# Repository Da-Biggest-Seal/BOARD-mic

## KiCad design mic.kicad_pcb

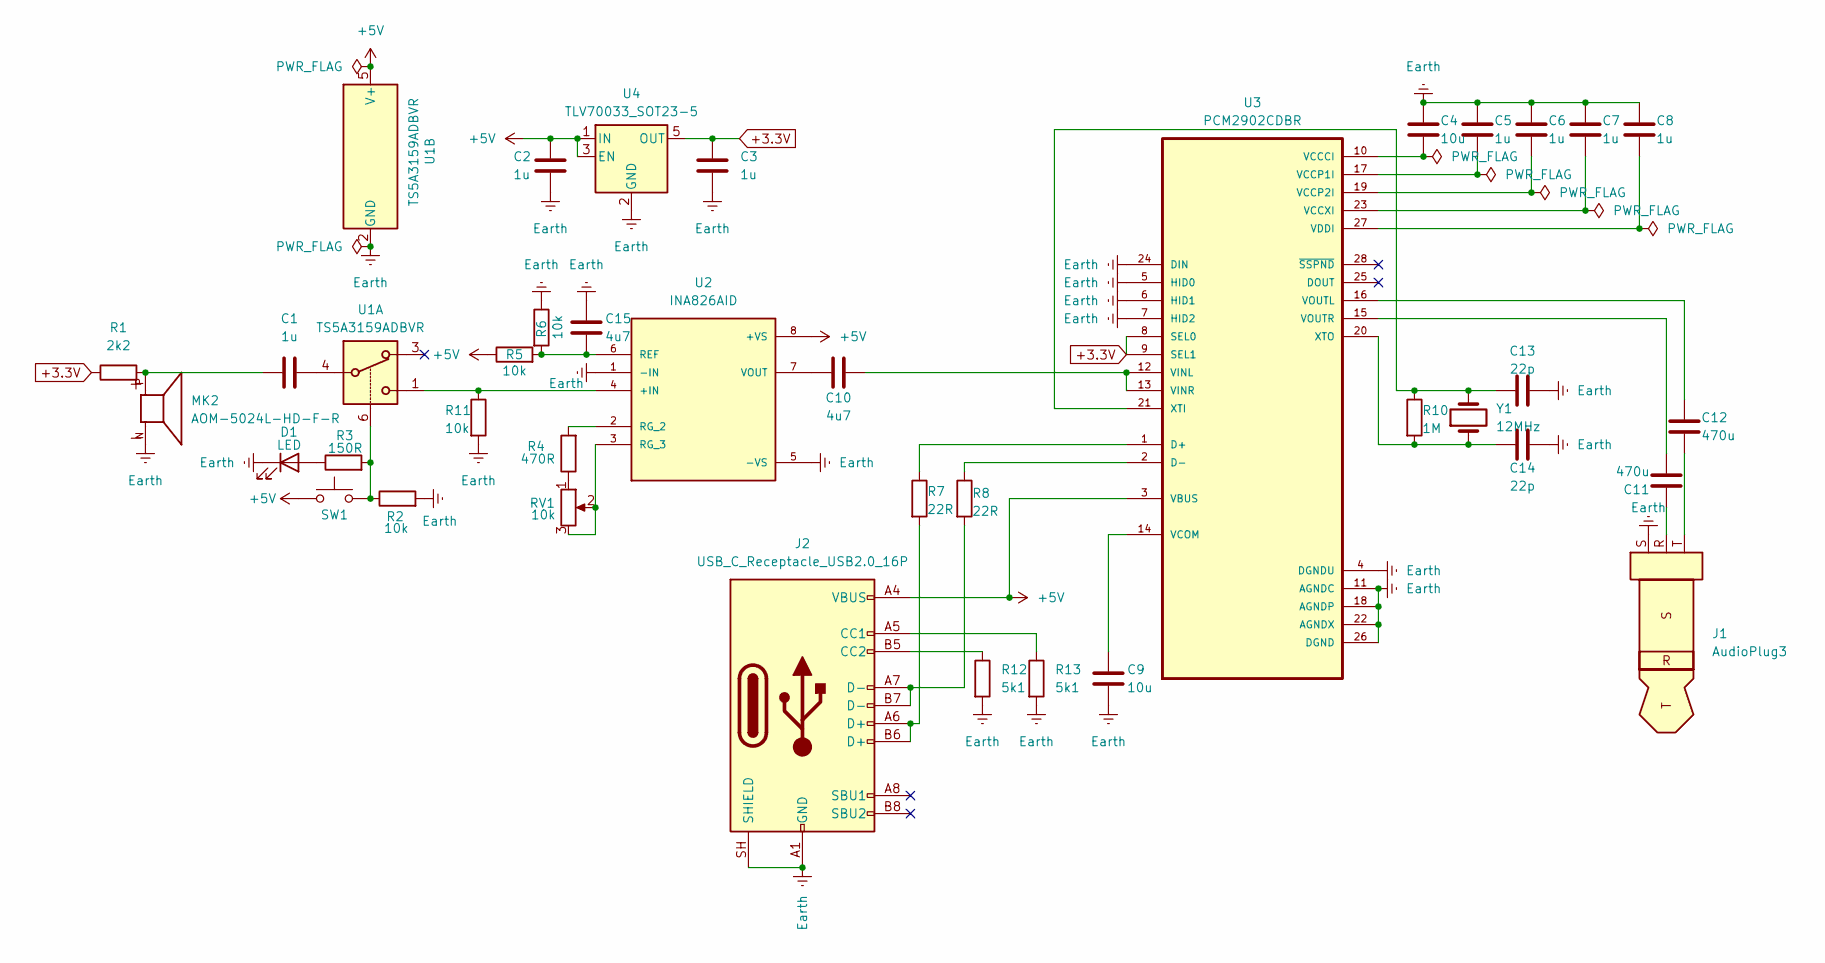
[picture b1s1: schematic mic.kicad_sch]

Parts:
C1, C2, C3, C5, C6, C7, C8: 1u; C_Disc_D3.4mm_W2.1mm_P2.50mm
C4, C9: 10u; C_Disc_D3.4mm_W2.1mm_P2.50mm
C10, C15: 4u7; C_Disc_D3.4mm_W2.1mm_P2.50mm
C11, C12: 470u; CP_Radial_D8.0mm_P3.50mm
C13, C14: 22p; C_Disc_D3.4mm_W2.1mm_P2.50mm
D1: LED; LED_D1.8mm_W1.8mm_H2.4mm_Horizontal_O1.27mm_Z1.6mm
J1: AudioPlug3; Jack_3.5mm_QingPu_WQP-PJ398SM_Vertical_CircularHoles; LCSC C22355828
J2: USB_C_Receptacle_USB2.0_16P; USB_C_Receptacle_G-Switch_GT-USB-7051x
MK2: AOM-5024L-HD-F-R; MIC_AOM-5024L-HD-F-R; PARTREV A
R1: 2k2; R_Axial_DIN0204_L3.6mm_D1.6mm_P2.54mm_Vertical
R2, R5, R6, R11: 10k; R_Axial_DIN0204_L3.6mm_D1.6mm_P2.54mm_Vertical
R3: 150R; R_Axial_DIN0204_L3.6mm_D1.6mm_P2.54mm_Vertical
R4: 470R; R_Axial_DIN0204_L3.6mm_D1.6mm_P2.54mm_Vertical
R7, R8: 22R; R_Axial_DIN0204_L3.6mm_D1.6mm_P2.54mm_Vertical
R10: 1M; R_Axial_DIN0204_L3.6mm_D1.6mm_P2.54mm_Vertical
R12, R13: 5k1; R_Axial_DIN0204_L3.6mm_D1.6mm_P2.54mm_Vertical
RV1: 10k; Potentiometer_Alps_RK097_Single_Horizontal
SW1: SW_Push; SW_Tactile_SPST_Angled_PTS645Vx58-2LFS
U1: TS5A3159ADBVR; SOT-23-6
U2: INA826AID; SOIC127P599X175-8N; PARTREV G; DigiKey_Part_Number 296-33294-5-ND
U3: PCM2902CDBR; SOP65P780X200-28N; DigiKey_Part_Number 2156-PCM2902CDBR-ND
U4: TLV70033_SOT23-5; SOT-23-5
Y1: 12MHz; Crystal_C26-LF_D2.1mm_L6.5mm_Vertical

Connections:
+3.3V: C3.1, R1.1, U3.8 (SEL0), U3.9 (SEL1), U4.5 (OUT)
+5V: C2.2, J2.A4 (VBUS), J2.A9 (VBUS), J2.B4 (VBUS), J2.B9 (VBUS), R5.1, SW1.1, U1.5 (V+), U2.8 (+VS), U3.3 (VBUS), U4.1 (IN), U4.3 (EN)
Earth: C2.1, C3.2, C4.1, C5.1, C6.1, C7.1, C8.1, C9.2, C13.2, C14.2, C15.1, D1.1 (K), J1.S, J2.A1 (GND), J2.A12 (GND), J2.B1 (GND), J2.B12 (GND), J2.SH (SHIELD), MK2.N, R2.2, R6.1, R11.2, R12.2, R13.2, U1.2 (GND), U2.1 (-IN), U2.5 (-VS), U3.4 (DGNDU), U3.5 (HID0), U3.6 (HID1), U3.7 (HID2), U3.11 (AGNDC), U3.18 (AGNDP), U3.22 (AGNDX), U3.24 (DIN), U3.26 (DGND), U4.2 (GND)
unnamed: C1.1, MK2.P, R1.2
unnamed: C1.2, U1.4
unnamed: C11.1, J1.R
unnamed: C12.2, J1.T
unnamed: D1.2 (A), R3.1
unnamed: J2.A5 (CC1), R13.1
unnamed: J2.B5 (CC2), R12.1
unnamed: J2.A6 (D+), J2.B6 (D+), R7.2
unnamed: J2.A7 (D-), J2.B7 (D-), R8.2
unnamed: R2.1, R3.2, SW1.2, U1.6
unnamed: R4.1, RV1.1
unnamed: R11.1, U1.1, U2.4 (+IN)
unnamed: C15.2, R5.2, R6.2, U2.6 (REF)
unnamed: R4.2, U2.2 (RG_2)
unnamed: RV1.2, RV1.3, U2.3 (RG_3)
unnamed: C10.2, U2.7 (VOUT)
unnamed: R7.1, U3.1 (D+)
unnamed: R8.1, U3.2 (D-)
unnamed: C4.2, U3.10 (VCCCI)
unnamed: C5.2, U3.17 (VCCP1I)
unnamed: C6.2, U3.19 (VCCP2I)
unnamed: C7.2, U3.23 (VCCXI)
unnamed: C9.1, U3.14 (VCOM)
unnamed: C8.2, U3.27 (VDDI)
unnamed: C10.1, U3.12 (VINL), U3.13 (VINR)
unnamed: C12.1, U3.16 (VOUTL)
unnamed: C11.2, U3.15 (VOUTR)
unnamed: C13.1, R10.1, U3.21 (XTI), Y1.2
unnamed: C14.1, R10.2, U3.20 (XTO), Y1.1

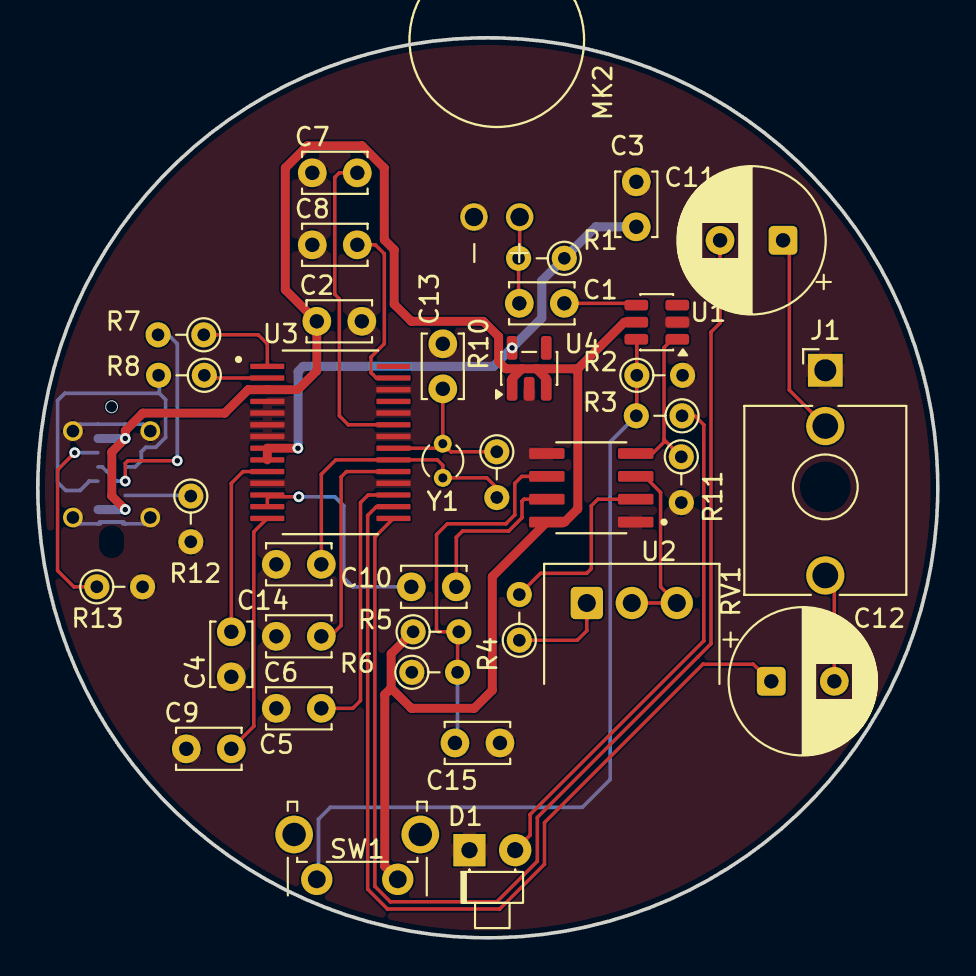
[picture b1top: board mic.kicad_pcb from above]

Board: 2 copper layers, 50.0 x 50.0 mm, 38 parts (1 on the bottom side), 32 nets.
